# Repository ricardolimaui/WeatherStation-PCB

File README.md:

# Unparallel Weather Station PCB

The Unparallel Weather Station allows anyone to build their own low-cost weather station, using our custom open-source PCB. The software for the weather station is also open-source and can be used as is, or freely customized to meet your own needs and requirements. A model for printing a 3D case for your weather station is also provided.

This Weather Station PCB is a board to simplify the assembly of a weather station using low-cost hardware and a LoPy4 board. The LoPy4 board is equipped with several connectivity options (e.g. Sigfox, LoRa, Wi-Fi and Bluetooth). Currently, the weather station uses Sigfox and/or Wi-Fi to send the data to the cloud, however, the software can be extended to support other connectivity options. A Grafana dashboard is then used to display the historical weather data that is stored on the cloud.

The weather station uses an external sensor (AM2315) for reading temperature and relative humidity, a weather meter kit (SEN-15901) for wind speed, wind direction and precipitation. The weather station is powered from a Li-Ion battery that is charged with a photovoltaic panel which is also used to measure solar radiation. Due to the system’s low-power operation and solar energy harvesting features, it is energy autonomous and can be deployed in remote places.

## Measured parameters:  
*	Temperature (ºC)
*	Relative Humidity (%)
*	Rain (mm/h)
*	Wind Speed (km/h)
*	Wind Gust Speed (km/h)
*	Wind Direction (degrees)
*	Wind Gust Direction (degrees)
*	Solar Radiation (W/m2)
*	Battery Voltage (V)

## Parts list:  
*	Unparallel Weather Station PCB
*	Unparallel Weather Station 3D printed case (optional)
*	AM2315 - Encased I2C Temperature/Humidity Sensor
*	Weather Meter Kit - SEN-15901
*	Li-Ion battery (recommended 3.65V; 8Ah)
*	2.5W Solar Panel (116x160mm)
*	Sigfox antenna (868MHz)
*	LoPy 4.0

This work was done in the context of SmartAgriHubs Research Project, which has received funding from the European Union’s Horizon 2020 research and innovation programme under grant agreement No 818182

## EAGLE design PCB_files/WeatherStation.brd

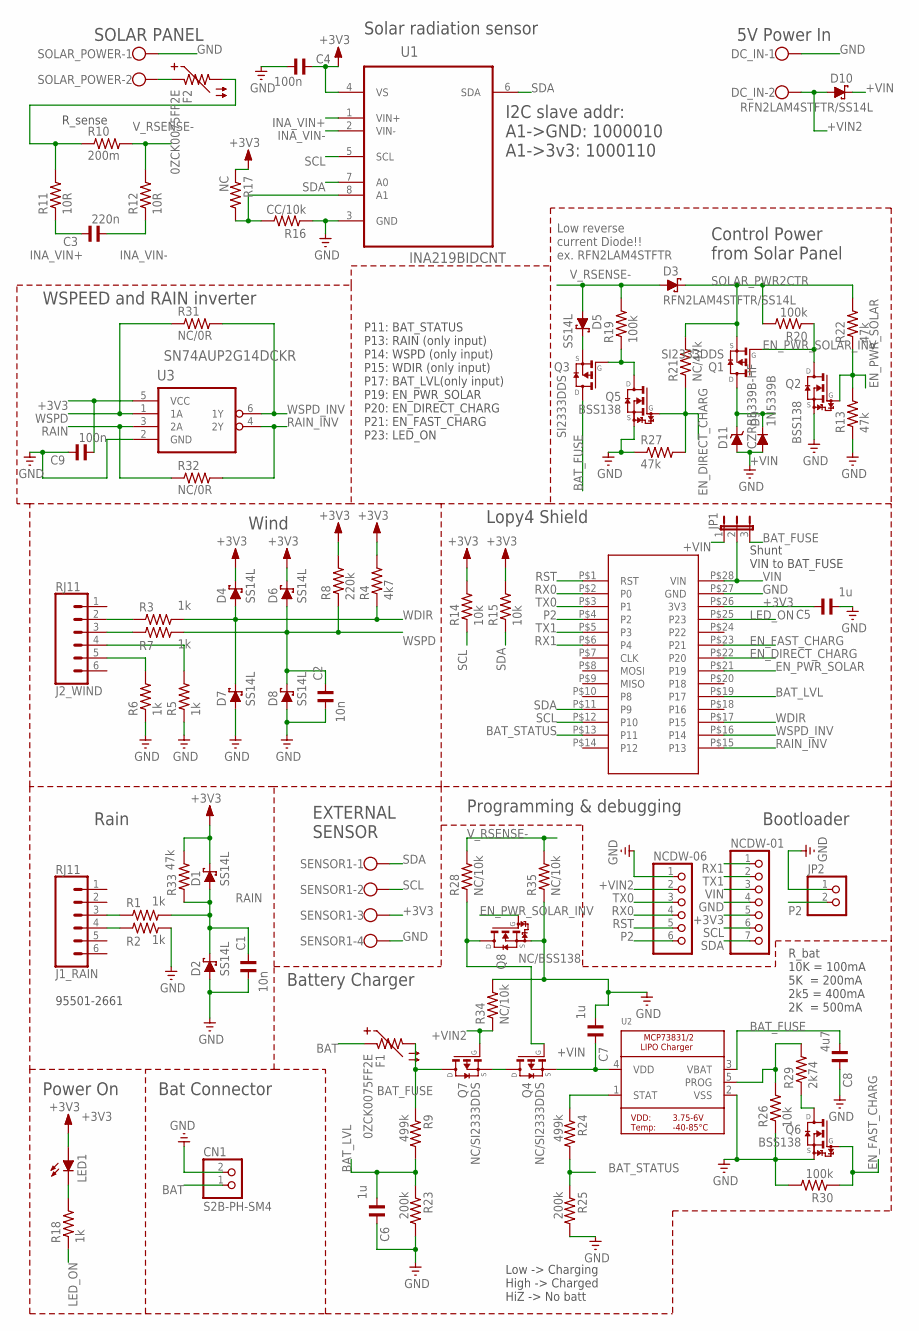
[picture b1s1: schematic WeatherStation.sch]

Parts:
C1, C2: 10n; C0603/C0805_PROTO_SLIM
C3: 220n; C0603
C4, C9: 100n; C0603
C5, C6, C7: 1u; C0603/C0805_PROTO_SLIM
C8: 4u7; C0603/C0805_PROTO_SLIM
CN1: S2B-PH-SM4; JST-PH-2-SMT-RA
D1, D2, D4, D5, D6, D7, D8: SS14L; SUB_SMA_PROTO
D3, D10: RFN2LAM4STFTR/SS14L; SMA_SOD-128_PROTO
D9: 1N5339B; DO15-12
D11: CZRB5339B-HF; SMB_PROTO
DC_IN: W237-102
F1: 0ZCK0075FF2E; R0603/R0805_PROTO_SLIM
F2: 0ZCK0075FF2E; R0805
J1_RAIN, J2_WIND: RJ11; RJ11-6
JP1: JP2E-0805; R0805/2
JP2: PINHD-1X2; 1X02
LED1: LEDCHIP-LED0805; CHIP-LED0805
NCDW-01: PINHD-1X7; 1X07
NCDW-06: PINHD-1X6; 1X06
Q1, Q3: SI2333DDS; SOT23_PROTO_SLIM
Q2, Q5, Q6: BSS138; SOT23_PROTO_SLIM
Q4, Q7: NC/SI2333DDS; SOT23_PROTO_SLIM
Q8: NC/BSS138; SOT23_PROTO_SLIM
R1, R2, R3, R5, R6, R7, R18: 1k; R0603
R4: 4k7; R0603/R0805_PROTO_SLIM
R8: 220k; R0603/R0805_PROTO_SLIM
R9, R24: 499k; R0603/R0805_PROTO_SLIM
R10: 200m; R0603/R0805_PROTO_SLIM
R11, R12: 10R; R0603
R13, R22, R27, R33: 47k; R0603
R14, R15: 10k; R0603
R16: CC/10k; R0603
R17: NC; R0603
R19, R20: 100k; R0603
R21: NC/47k; R0603
R23, R25: 200k; R0603/R0805_PROTO_SLIM
R26: 10k; R0603/R0805_PROTO_SLIM
R28, R34, R35: NC/10k; R0603
R29: 2k74; R0603/R0805_PROTO_SLIM
R30: 100k; R0603/R0805_PROTO_SLIM
R31, R32: NC/0R; R0603/R0805_PROTO_SLIM
SENSOR1: W237-4
SOLAR_POWER: W237-102
U1: INA219BIDCNT; SOT65P280X145-8N
U2: MCP73831/2; SOT23-5
U3: SN74AUP2G14DCKR; SOT65P210X110-6N_EDIT
U$2: LOPY4_SHIELD

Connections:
+3V3: C4.1, C5.1, C9.2, D1.C, D4.C, D6.C, LED1.A, NCDW-01.5, R4.2, R8.2, R14.2, R15.2, R17.1, R33.2, SENSOR1.3, U1.4 (VS), U3.5 (VCC), U$2.P$26 (3V3)
+VIN: C7.1, D9.C, D10.C, D11.C, JP1.1, Q1.3 (D), Q4.2 (S), U2.4 (VDD)
+VIN2: D10.A, DC_IN.2, NCDW-06.2, Q7.1 (G), R34.1
BAT: CN1.1 (2), F1.1
BAT_FUSE: C8.2, F1.2, JP1.3, Q3.3 (D), Q7.3 (D), R9.1, U2.3 (VBAT)
BAT_LVL: C6.2, R9.2, R23.1, U$2.P$19 (P17)
BAT_STATUS: R24.2, R25.1, U$2.P$13 (P11)
EN_DIRECT_CHARG: Q5.1 (G), R21.1, R27.2, U$2.P$22 (P20)
EN_FAST_CHARG: Q6.1 (G), R30.1, U$2.P$23 (P21)
EN_PWR_SOLAR: Q2.1 (G), R13.2, R22.1, U$2.P$21 (P19)
EN_PWR_SOLAR_INV: Q1.1 (G), Q2.3 (D), Q8.1 (G), R20.1
GND: C1.2, C2.2, C4.2, C5.2, C6.1, C7.2, C8.1, C9.1, CN1.2 (1), D2.A, D7.A, D8.A, D9.A, D11.A, DC_IN.1, JP2.1, NCDW-01.4, NCDW-06.1, Q2.2 (S), Q5.2 (S), Q6.2 (S), Q8.2 (S), R2.2, R5.1, R6.1, R13.1, R16.1, R23.2, R25.2, R26.1, R27.1, R30.2, R34.2, R35.1, SENSOR1.4, SOLAR_POWER.1, U1.3 (GND), U2.2 (VSS), U3.2 (GND), U$2.P$27 (GND)
INA_VIN+: C3.1, R11.1, U1.1 (VIN+)
INA_VIN-: C3.2, R12.1, U1.2 (VIN-)
LED_ON: R18.1, U$2.P$25 (P23)
unnamed: D5.C, Q3.2 (S)
unnamed: F2.1, SOLAR_POWER.2
unnamed: J1_RAIN.4, R2.1
unnamed: J1_RAIN.3, R1.1
unnamed: J2_WIND.2, R3.1
unnamed: J2_WIND.3, R7.1
unnamed: J2_WIND.4, R5.2
unnamed: J2_WIND.5, R6.2
unnamed: Q4.1 (G), Q8.3 (D), R28.1
unnamed: R26.2, R29.2, U2.5 (PROG)
unnamed: R16.2, R17.2, U1.8 (A1)
unnamed: LED1.C, R18.2
unnamed: Q6.3 (D), R29.1
unnamed: Q3.1 (G), Q5.3 (D), R19.1
unnamed: R24.1, U2.1 (STAT)
unnamed: Q4.3 (D), Q7.2 (S)
P2: JP2.2, NCDW-06.6, U$2.P$4 (P2)
RAIN: C1.1, D1.A, D2.C, R1.2, R32.1, R33.1, U3.3 (2A)
RAIN_INV: R32.2, U3.4 (2Y), U$2.P$15 (P13)
RST: NCDW-06.5, U$2.P$1 (RST)
RX0: NCDW-06.4, U$2.P$2 (P0)
RX1: NCDW-01.1, U$2.P$6 (P4)
SCL: NCDW-01.6, R14.1, SENSOR1.2, U1.5 (SCL), U$2.P$12 (P10)
SDA: NCDW-01.7, R15.1, SENSOR1.1, U1.6 (SDA), U1.7 (A0), U$2.P$11 (P9)
SOLAR_PWR2CTR: D3.C, Q1.2 (S), R20.2, R21.2, R22.2
TX0: NCDW-06.3, U$2.P$3 (P1)
TX1: NCDW-01.2, U$2.P$5 (P3)
VBUS_SOLAR: F2.2, R10.1, R11.2
VIN: JP1.2, NCDW-01.3, U$2.P$28 (VIN)
V_RSENSE-: D3.A, D5.A, R10.2, R12.2, R19.2, R28.2, R35.2
WDIR: D4.A, D7.C, R3.2, R4.1, U$2.P$17 (P15)
WSPD: C2.1, D6.A, D8.C, R7.2, R8.1, R31.1, U3.1 (1A)
WSPD_INV: R31.2, U3.6 (1Y), U$2.P$16 (P14)

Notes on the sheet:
Lopy4 Shield
EXTERNAL SENSOR
SOLAR PANEL
Rain
Wind
Solar radiation sensor
I2C slave addr: A1->GND: 1000010 A1->3v3: 1000110
Power On
5V Power In
P11: BAT_STATUS P13: RAIN (only input) P14: WSPD (only input) P15: WDIR (only input) P17: BAT_LVL(only input) P19: EN_PWR_SOLAR P20: EN_DIRECT_CHARG P21: EN_FAST_CHARG P23: LED_ON
Programming & debugging
Control Power from Solar Panel
R_bat 10K = 100mA 5K = 200mA 2k5 = 400mA 2K = 500mA
Low -> Charging High -> Charged HiZ -> No batt
Battery Charger
Bootloader
R_sense
95501-2661
Low reverse current Diode!! ex. RFN2LAM4STFTR
WSPEED and RAIN inverter
Bat Connector
Shunt VIN to BAT_FUSE

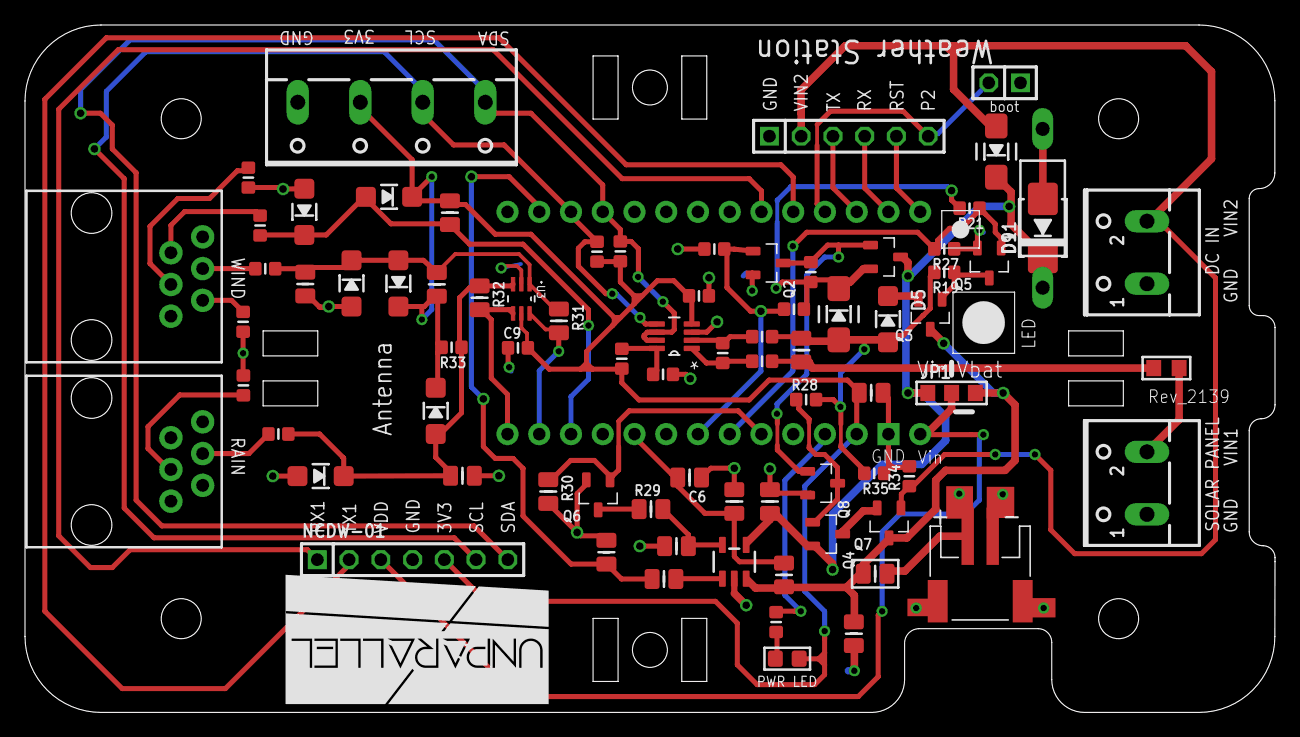
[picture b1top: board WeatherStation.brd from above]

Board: 2 copper layers, 100.0 x 55.0 mm, 83 parts (0 on the bottom side), 48 nets.

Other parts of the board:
STAND2, STAND3: MOUNTHOLE_110MIL
U$1: UNPARALLEL_LOGO_NEW_0_INVERT_BIG

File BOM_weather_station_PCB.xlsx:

Qty per brd | Value | Device | Schematic Reference | Manufacturer Part Number (MPN) | MFR | Description
1 | - | LEDCHIP-LED0805 | LED1 | LG R971-KN-1 | Osram Opto Semiconductor | Standard LEDs - SMD 0805 Green, 570nm 26mcd, 20mA
1 | - | MCP73831/2 | U2 | MCP73831T-2ACI/OT | Microchip | Battery Management Charge
1 | - | PINHD-1X2 | JP2 | DS1023-1*2S21 | CONNFLY | Female; PIN: 2; straight; 2.54mm; THT; 1x2; 3A
1 | - | PINHD-1X6 | NCDW-06 | DS1023-1*6S21 | CONNFLY | Female; PIN: 6; straight; 2.54mm; THT; 1x6; 3A
2 | - | W237-102 | DC_IN SOLAR_POWER | DG300-5.0-2P12 | DEGSON ELECTRONICS | PCB terminal block; angled 90°; 5mm; ways: 2; on PCBs; 2.5mm2; 24A
2 | - | W237-4 | SENSOR1 | DG300-5.0-2P12 | DEGSON ELECTRONICS | PCB terminal block; angled 90°; 5mm; ways: 2; on PCBs; 2.5mm2; 24A
3 | 100k | R-EU_R0603 | R19 R20 R30 | RC0603FR-07100KL | YAGEO | Thick Film Resistors - SMD 0603 100 kOhms 100mW 0603 1%
2 | 100n | C-EUC0603 | C4 C9 | CC0603KRX7R8BB104 | YAGEO | MLCC - SMD/SMT 0603 25V 0.1uF X7R 0603 10%
2 | 10R | R-EU_R0603 | R11 R12 | CRCW060310R0FKEAC | Vishay | Thick Film Resistors - SMD 0603 1/10Watt 10ohms 1% Commercial Use
3 | 10k | R-EU_R0603 | R14 R15 R26 | CR0603-FX-1002ELF | Bourns | Thick Film Resistors - SMD 0603 10K 1% 1/10W
2 | 10n | C-EUC0603/C0805_PROTO | C1 C2 | 885012206089 | Wurth Elektronik | MLCC - SMD/SMT WCAP-CSGP 0.01uF 0603 10% 50V
7 | 1k | R-EU_R0603 | R1 R2 R3 R5 R6 R7 R18 | CR0603-FX-1001ELF | Bourns | Thick Film Resistors - SMD 0603 1K 1% 1/10W
1 | 2k74 | R-EU_R0603/R0805_PROTO | R29 | RC0603FR-132K74L | YAGEO | Thick Film Resistors - SMD 0603 2.74kOhms 1/10W 0603 1%
3 | 1u | C-EUC0603/C0805_PROTO | C5 C6 C7 | C0805C105K3RACTU | KEMET | MLCC - SMD/SMT 25V 1uF X7R 0805 10%
2 | 200k | R-EU_R0603/R0805_PROTO | R23 R25 | CRCW0603200KFKEAC | Vishay | Thick Film Resistors - SMD 0603 1/10Watt 200Kohms 1%
1 | 200m | R-EU_R0603/R0805_PROTO | R10 | RL1220S-R20-F | Susumu | Current Sense Resistors - SMD 0805 1/3W 0.20ohm 1%
1 | 220n | C-EUC0603 | C3 | CC0603KRX7R7BB224 | YAGEO | MLCC - SMD/SMT 16V 0.22uF X7R 0603 10%
4 | 47k | R-EU_R0603 | R13 R22 R27 R33 | RC0603FR-0747KL | YAGEO | Thick Film Resistors - SMD 47 kOhms 100mW 0603 1%
2 | 499k | R-EU_R0603/R0805_PROTO | R9 R24 | CR0603-FX-4993ELF | Bourns | Thick Film Resistors - SMD 499K ohm 1%
1 | 4k7 | R-EU_R0603/R0805_PROTO | R4 | RC0603FR-074K7L | YAGEO | Thick Film Resistors - SMD 4.7 kOhms 100mW 0603 1%
1 | 4u7 | C-EUC0603/C0805_PROTO | C8 | GRM21BZ7YA475KE15L | Murata | MLCC - SMD/SMT 35V 4.7uF X7R 0805 10%
3 | BSS138 | BSS138 | Q2 Q5 Q6 | BSS138-7-F | Diodes Incorporated | MOSFET 300mW 50V DSS SOT-23-3 N-channel
1 | CC/10k | R-EU_R0603 | R16 | Soldering Shunt
1 | CZRB5339B-HF | ZENER-DIODE-PROTO | D11 or D9 | CZRB5339B-HF Or 1N5339B-TP | Comchip Technology Or Micro Commercial Components (MCC) | Zener Diodes ZENER 5W 5.6V SMB DO-214AA-2 Or Zener Diodes 5.0W 5.6V 1uA 865mA 1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
1 | INA219BIDCNT | INA219BIDCNT | U1 | INA219BIDCNR | Texas Instruments | Current & Power Monitors & Regulators 0-Drift,Bi-dir Current/Pwr Monitor
2 | LOPY4 pinheader | LOPY4_SHIELD | U$2 | DS1023-1*14S21 | CONNFLY | Female; PIN: 14; straight; 2.54mm; THT; 1x14; 3A |  |  |  |  |  |  |  |  |  | e.g. https://www.adafruit.com/product/2940
1 | 220k | R-EU_R0603/R0805_PROTO | R8 | RC0603FR-0722KL | YAGEO | Thick Film Resistors - SMD 22 kOhms 100mW 0603 1%
2 | 0ZCK0075FF2E | PTC-0805 | F1 F2 | 0ZCK0075FF2E | Bel | Resettable Fuses - PPTC Hold current 750 mA 0805
2 | RFN2LAM4STFTR/SS14L | SCHOTTKY-DIODESMA_SOD-128_PROTO | D3 D10 | RFN2LAM4STFTR | ROHM Semiconductor | Diodes 400V VR 1.5A IO SOD-128; PMDTM
2 | RJ11 | RJ11-6 | J1_RAIN J2_WIND | 95501-2661 | Molex | Ethernet Connectors RA 6/6 RJ12 LOW PROFILE THT
1 | S2B-PH-SM4 | JST_2PIN-SMT-RA | CN1 | S2B-PH-SM4-TB | JST | Male; PH; 2mm; PIN: 2; SMT
2 | SI2333DDS_PROTO | SI2333DDS_PROTO | Q1 Q3 | SI2333DDS-T1-GE3 | Vishay | Transistor: P-MOSFET; unipolar; -12V; -5.2A; Idm: -20A; 1.1W; SOT23
1 | SN74AUP2G14DCKR | SN74AUP2G14-DCKR | U3 | SN74AUP2G14DCKR | Texas Instruments | Inverters Lo-Pwr Dual Schmitt- Trigger Inverter SC70-6
7 | SS12L | SCHOTTKY-DIODESUB_SMA_PROTO | D1 D2 D4 D6 D7 D8 D5 | SS14L | Taiwan Semiconductor | Schottky Rectifiers Sub SMA-2
1 | CC |  | JP1 | Soldering Shunt to vbat

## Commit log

2021-09-27 Create PCB_files
2021-09-27 Create test
2021-09-27 Eagles files WeatherStation_0v9
2021-09-27 Gerber files WeatherStation_0v9
2021-09-27 BOM and parts list
2021-09-27 Add grant agreement

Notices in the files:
parts and their libraries:
SparkFun-Connectors: Licensing: Creative Commons ShareAlike 4.0 International - https://creativecommons.org/licenses/by-sa/4.0
